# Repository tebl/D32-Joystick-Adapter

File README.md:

# D32 Joystick Adapter
I don't have a joystick for any of my Dragon 32s, I actually have two of them - mostly because it's the little welsh machine that thought it could - then it actually did! Often mentioned as a copy of the more successful american, but from what I can see - both of them seem to be a rather straight-forward implementation of a Motorola reference design from the same period. Where I live the computer didn't see much success until after its actual demise, the reason being that they became available at a very low price of *a freaking lot of money* (I was very young at a time, so anything that wasn't, well, a small stack of coins was still a lot to me).

What I don't have however, is a working joystick for any of them. I can't buy one, mainly because according to someone very close to me - I appearantly have enough stuff! So I need to make some more - *all* by myself - *all by myself* (cue the music). Actually, I just searched around for a solution and with the power of Googles search engine at my fingertips - I copied the one from [vrai.net](http://vrai.net/retro/?p=112) and designed a PCB around it.

Anyway - I'm rambling again, but for those just tuning into the workings of my basement laboratory - this project is about making an adapter so standard Atari 9-pin joysticks can be used with the Dragon 32 (also sold as the Tano Dragon in America) and Dragon 64 computers. In theory it could work for the TRS-80 Colour Computer (CoCo), but I don't have one - so until the day someone just gives me one, I can't test it. The finished project, including an optional faceplate can be seen above.

- [1> BOM](#1-bom)
  - [1.1>D32 Joystick Adapter](#11-d32-joystick-adapter)
  - [1.2> D32 Joystick Adapter (Faceplate)](#12-d32-joystick-adapter-faceplate)
- [2> Building the D32 Joystick Adapter](#2-building-the-d32-joystick-adapter)
  - [2.1> Testing it out](#21-testing-it-out)

# 1> BOM
This is the list of parts that you'd need in order to construct a D32 Joystick Adapter, most if not all should be readily available from your friendly neighbourhood electronics store if you should happen to have one available to you. For me, that means ebay since those kind of stores disappeared in the 80s around here - your mileage may wary (and so may the actual friendliness).

I've separated the parts belonging to the actual module into section 1.1, the faceplate is strictly optional and has no active components - I'm just having fun making these, so unless you want one you don't really need the components listed.

## 1.1> D32 Joystick Adapter
| Reference                 | Item                                  | Count | Order  |
| ------------------------- | ------------------------------------- | ----- | ------ |
| D32 Joystick Adapter PCB  | Fabricate using Gerber files          |     1 | [PCBWay](https://www.pcbway.com/project/shareproject/D32_Joystick_Adapter.html) |
| J1 *                      | Male 240° connector and 5-core wire   |     1 |        |
| J2                        | Male DB9 right-angle connector        |     1 |        |
| JP1 **                    | 1x2 pin right-angle header and jumper |     1 |        |
| R1,R3,R5,R7               | 10k Ohm resistor                      |     4 |        |
| R2,R4,R6,R8               | 47k Ohm resistor                      |     4 |        |
| U1                        | CD4066 (DIP-14)                       |     1 |        |

*) Note that this isn't actually a PCB-component, you're supposed to solder the male connector at the other end of the cable. One cheap source of these cables is either purchasing a cheap RS232 cable and cutting off both ends. Use a cable tie as strain relief.

**) This was added so that VCC could be removed from the cable if needed, the *C64 JoyKEY* when including the Arduino drags down the line a bit too much. If you only intend to use regular Atari-style joysticks, feel free to install a piece of wire shorting this instead.

## 1.2> D32 Joystick Adapter (Faceplate)
| Reference                 | Item                                  | Count | Order  |
| ------------------------- | ------------------------------------- | ----- | ------ |
| Faceplate A1 (PCB) *      | Fabricate using Gerber files          |     1 | [PCBWay](https://www.pcbway.com/project/shareproject/D32_Joystick_Adapter__Faceplate_.html) |
| Faceplate A2 (PCB) *      | Fabricate using Gerber files          |     1 | [PCBWay](https://www.pcbway.com/project/shareproject/D32_Joystick_Adapter__Faceplate_A2_.html) |
| Mounting **               | M3x8mm Nylon Hex standoff             |     4 |        |
|                           | M3x6mm nylon screw                    |     4 |        |

*) The A1 and A2 faceplates serve the same function, so you will only need one of them. The A1 faceplate is the Dragon-themed one, A2 has something that should have a larger appeal to our American friends with access to a RadioShack TRS-80 Colour Computer.

**) The suggested nylon standoff should be common values, if you have one of the cheap M3 nylon standoff kits sold on ebay and similar site - feel free to try out whichever works best for you. Keeping within the limits of the kit I'd use the 8mm standoffs, use screws on top and nuts on the underside (cut off the remainder of the screw poking through).

# 2> Building the D32 Joystick Adapter
Building the *D32 Joystick Adapter* should for the most part be an easy affair for most with access to a decent set of tools, burn-proof fingers and a deep-seeded interest in playing games on a Dragon 32 using an Atari-style joystick. Start by reading through the BOM above for a list of all parts required, order what you don't already have tucked into a drawer, chest or the back of the sofa cushions - wherever you keep yours. Everything? Read on for the exciting conclusion to project *"clicky joy with the Dragon 32"*.

Still here? Excellent.

As pictured above, where I've already done most of the work you can see the finished module. There are many roads to getting there, but the easiest is starting with the resistors - solder them in according to the values printed. Install a 14-pin socket for U1 as everyone hates removing non-functional chips, which is something that's a regularly common affair when ordering things from the non-professional electronic component vendors - they're usually cheaper than regular chips though.

At this point you could install the DB9-connector if you wanted, but I recommend paying attention to the cable install instead - the one with a picture of a DIN-plug on. As long as you've got a cable with enough cores and the ability to tell the wires apart, just pick a colour for each and solder them into place (I'm assuming there isn't a connector on the other end at this point). Use the two larger holes above to zip-tie the cable into place, this ensures that the cable doesn't come undone in the next few days.

Note that the pins on the PCB has been numbered for you, the connector will also have something similar on it. **BEFORE** continuing though, thread the sleeve onto the cable - failiure to do so means you'll have to desolder something tonight (might be either end of the cable). Use the PCB directions on the topside, back of plug view and match the coloured wires to the correct number. Use the numbering on the underside if you're attempting to match it to something that already has the correct connector attached, such as when upcycling the cable from a non-functioning joystick.

It is my hope that everything'll work out as it should, but before you connect it up to a Dragon 32 I highly recommend that you check for any direct shorts on the power side of things - this is easily done by checking for a lack of contiuity between U1 pins 7 and 14. If you opted for a faceplate, just screw it on using the standoffs listed in the BOM.

That should be every bit of knowledge I'm able to impart on you this evening, excuse the mistakes and exceptionally bad puns!

## 2.1> Testing it out
Going back to the hope we had in the building section, we now resort to my less than plug-and-pray way of attacking the project. Plug it into the computer, plug an Atari-style joystick into the **right** joystick - because why not do the right one? I got lazy on the script I borrowed from [dragon32forever](https://dragon32forever.wordpress.com/dragon-bytes/joysticks/), that's why. I've included it in the repository under [software](https://github.com/tebl/D32-Joystick-Adapter/tree/main/software), don't bother breaking out a DragonDrive or DragonMMC to load the thing - it is a tiny thing so just type it in.

Here's the next part: RUN

The script should flicker the screen a lot, but between the flickering you should see some numbers for the X- and Y-axis. It should display a number between 0 and 63, when pushing the joystick in all the ways it should jump between the extremes. When not pushing anything it should center somewhere along the middle (around 30).

I found that my [C64 JoyKEY](https://github.com/tebl/C64-JoyKEY) with an Arduino installed pulls the VCC-line too far down (my max value didn't go above 40) so it didn't work properly unless the VCC_EN jumper is removed, the Dragon 32 simply wasn't meant to power an Arduino and a bunch of LEDs via the joystick port - most common Atari-style joysticks with a sensible amount of circuitry should work properly.

Now go play some games, I recommend starting with either *Rommel's Revenge* or *Donkey King* - both worked pretty great for the 5 minutes I spent playing them. That's a pretty good statistic, I just prefer building things these days!

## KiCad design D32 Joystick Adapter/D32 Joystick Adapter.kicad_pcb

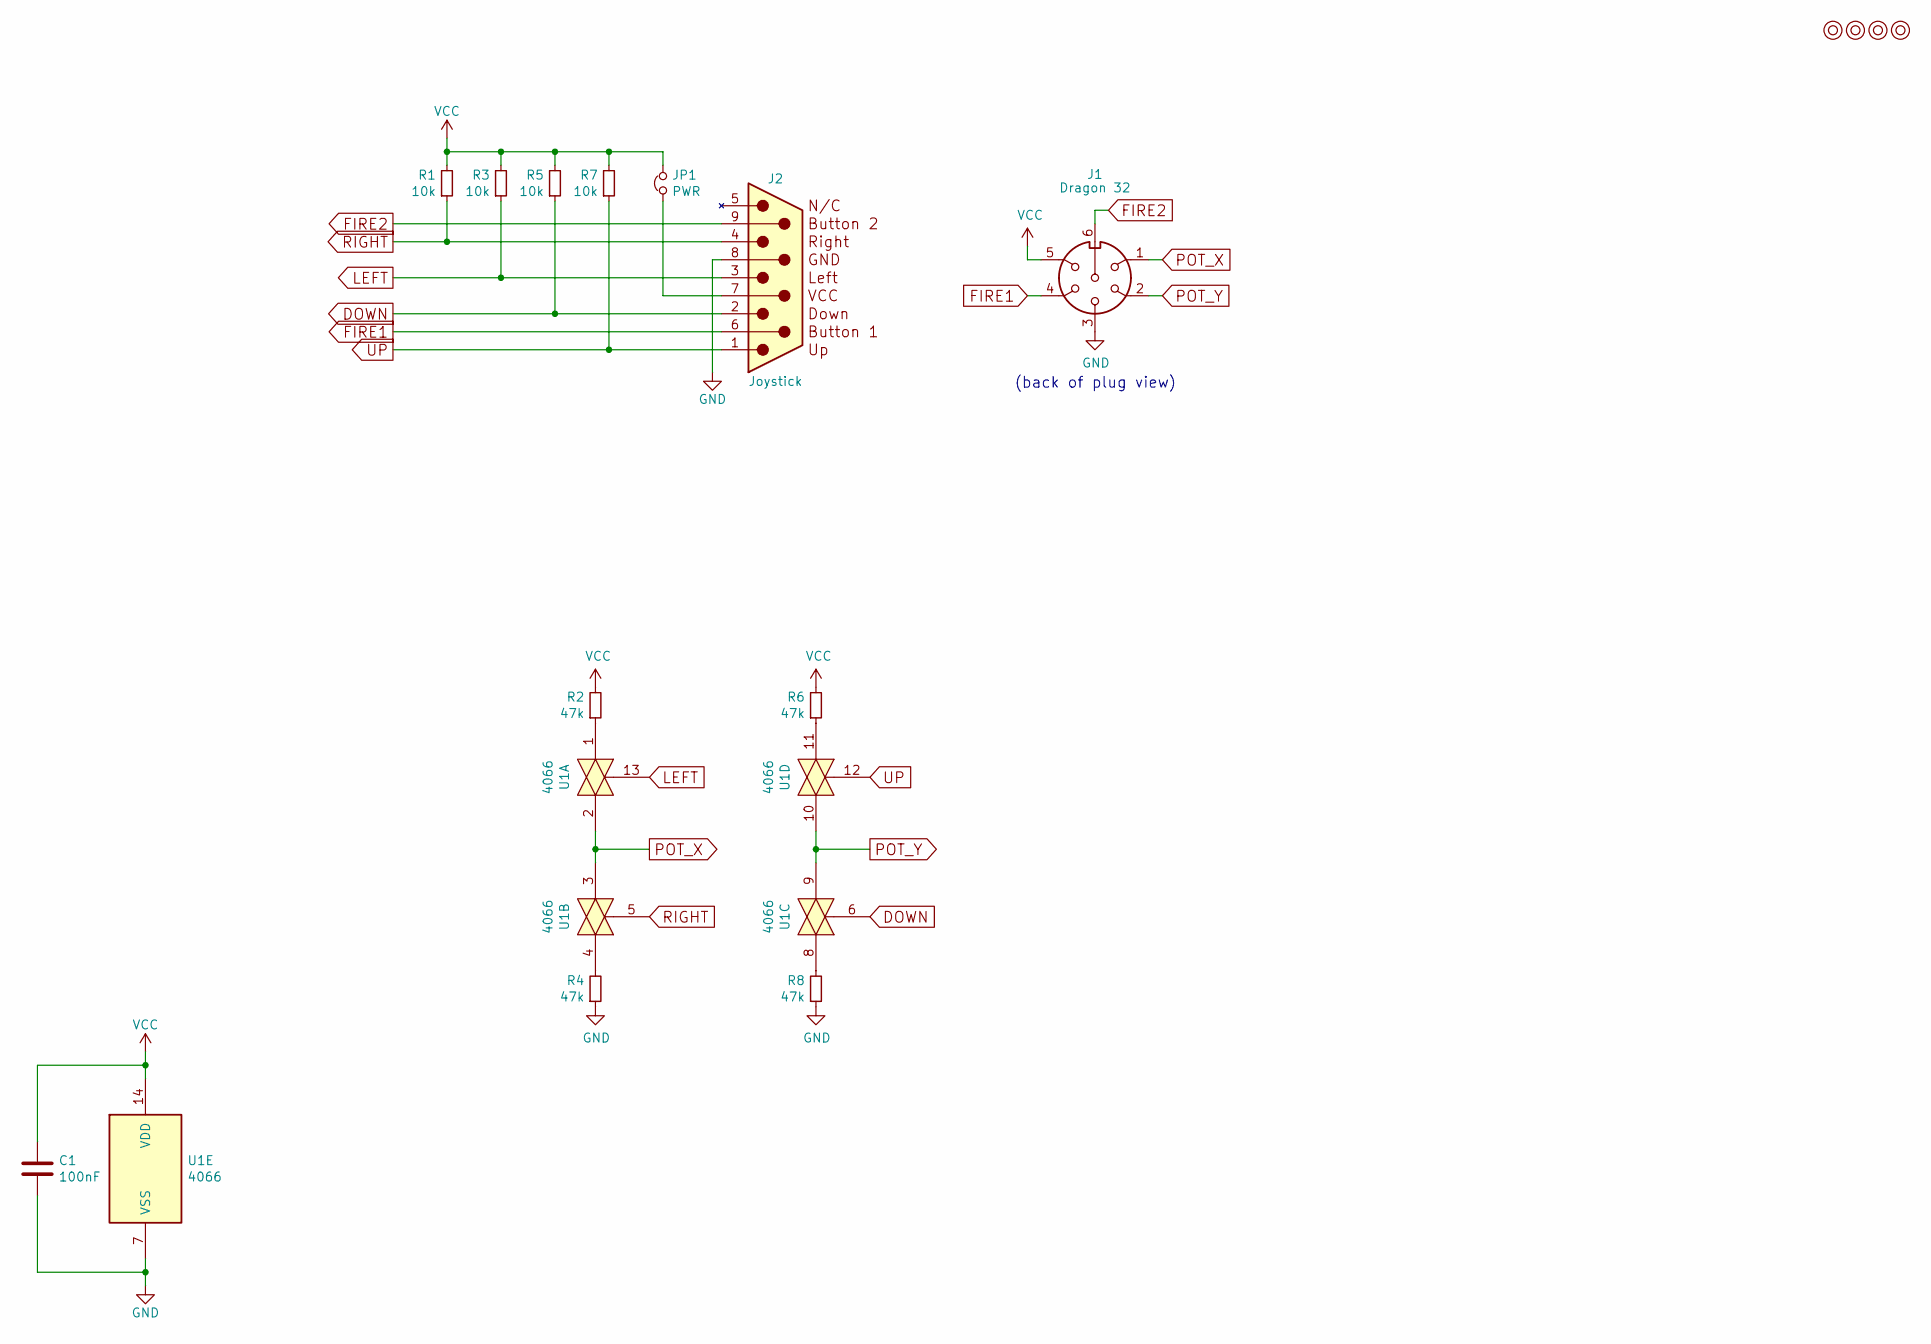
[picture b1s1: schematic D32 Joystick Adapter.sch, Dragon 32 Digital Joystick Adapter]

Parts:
C1: 100nF; C_Disc_D4.7mm_W2.5mm_P5.00mm
J1: Dragon 32; OUTPUT_ZIP
J2: Joystick; DSUB-9_Male_Horizontal_P2.77x2.84mm_EdgePinOffset7.70mm_Hou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
JP1: PWR; PinHeader_1x02_P2.54mm_Horizontal
M1, M2, M3, M4: Mounting; M3_pin
R1, R3, R5, R7: 10k; R_Axial_DIN0207_L6.3mm_D2.5mm_P10.16mm_Horizontal
R2, R4, R6, R8: 47k; R_Axial_DIN0207_L6.3mm_D2.5mm_P10.16mm_Horizontal
U1: 4066; DIP-14_W7.62mm_Socket_LongPads

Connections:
DOWN: J2.2, R5.1, U1.6
FIRE1: J1.4, J2.6
FIRE2: J1.6, J2.9
GND: C1.2, J1.3 (GND), J2.8 (GND), R4.1, R8.1, U1.7 (VSS)
LEFT: J2.3, R3.1, U1.13
unnamed: J2.7 (VCC), JP1.1
unnamed: R2.1, U1.1
unnamed: R4.2, U1.4
unnamed: R6.1, U1.11
unnamed: R8.2, U1.8
POT_X: J1.1, U1.2, U1.3
POT_Y: J1.2, U1.9, U1.10
RIGHT: J2.4, R1.1, U1.5
UP: J2.1, R7.1, U1.12
VCC: C1.1, J1.5 (VCC), JP1.2, R1.2, R2.2, R3.2, R5.2, R6.2, R7.2, U1.14 (VDD)

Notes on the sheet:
(back of plug view)

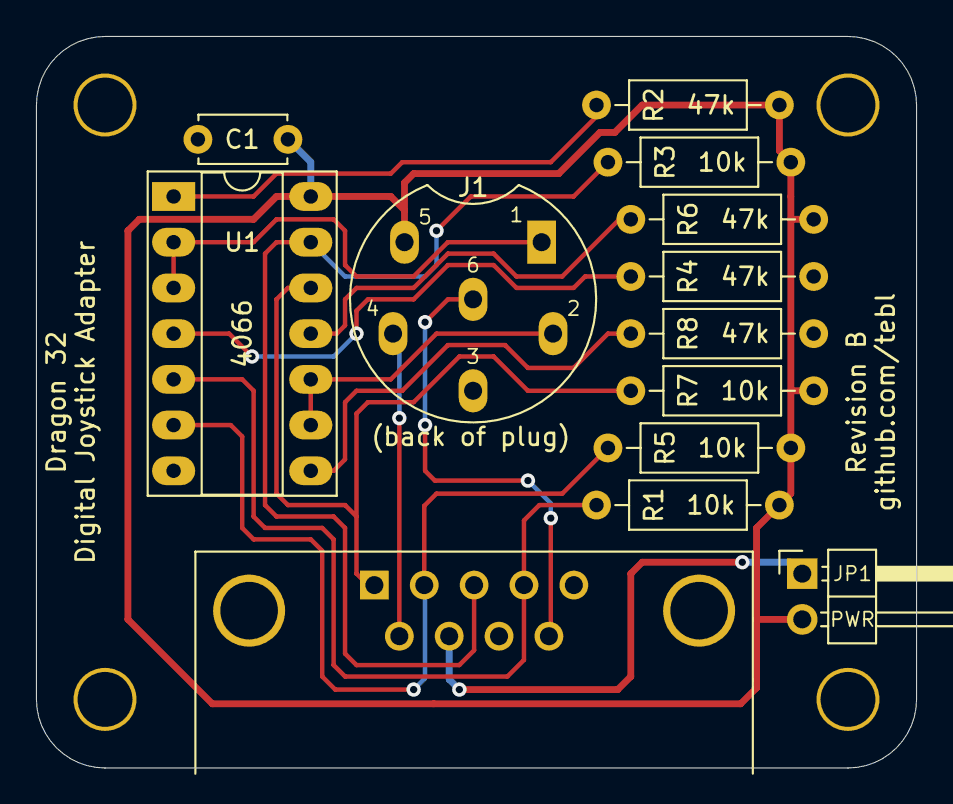
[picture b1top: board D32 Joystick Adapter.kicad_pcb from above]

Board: 2 copper layers, 48.9 x 40.6 mm, 17 parts (0 on the bottom side), 15 nets.

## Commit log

2021-01-12 Schematic done
2021-01-13 Layout done
2021-01-13 Faceplate logo
2021-01-17 Add faceplate
2021-01-19 Changed faceplate cutout
2021-01-20 Added pinout to silkscreen
2021-01-22 Added test program
2021-01-22 Added power jumper and changed resistor values
2021-01-23 Added images
2021-01-23 Moved test script
2021-01-23 Added README
2021-01-23 Added section links
2021-01-23 Added LICENSE text to PCB
2021-01-25 Added pictures
2021-01-26 Slightly more cutout space
2021-01-26 CoCo faceplate

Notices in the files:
D32 Joystick Adapter/D32 Joystick Adapter.kicad_pcb:
Licensed under
CERN OHL v1.2
